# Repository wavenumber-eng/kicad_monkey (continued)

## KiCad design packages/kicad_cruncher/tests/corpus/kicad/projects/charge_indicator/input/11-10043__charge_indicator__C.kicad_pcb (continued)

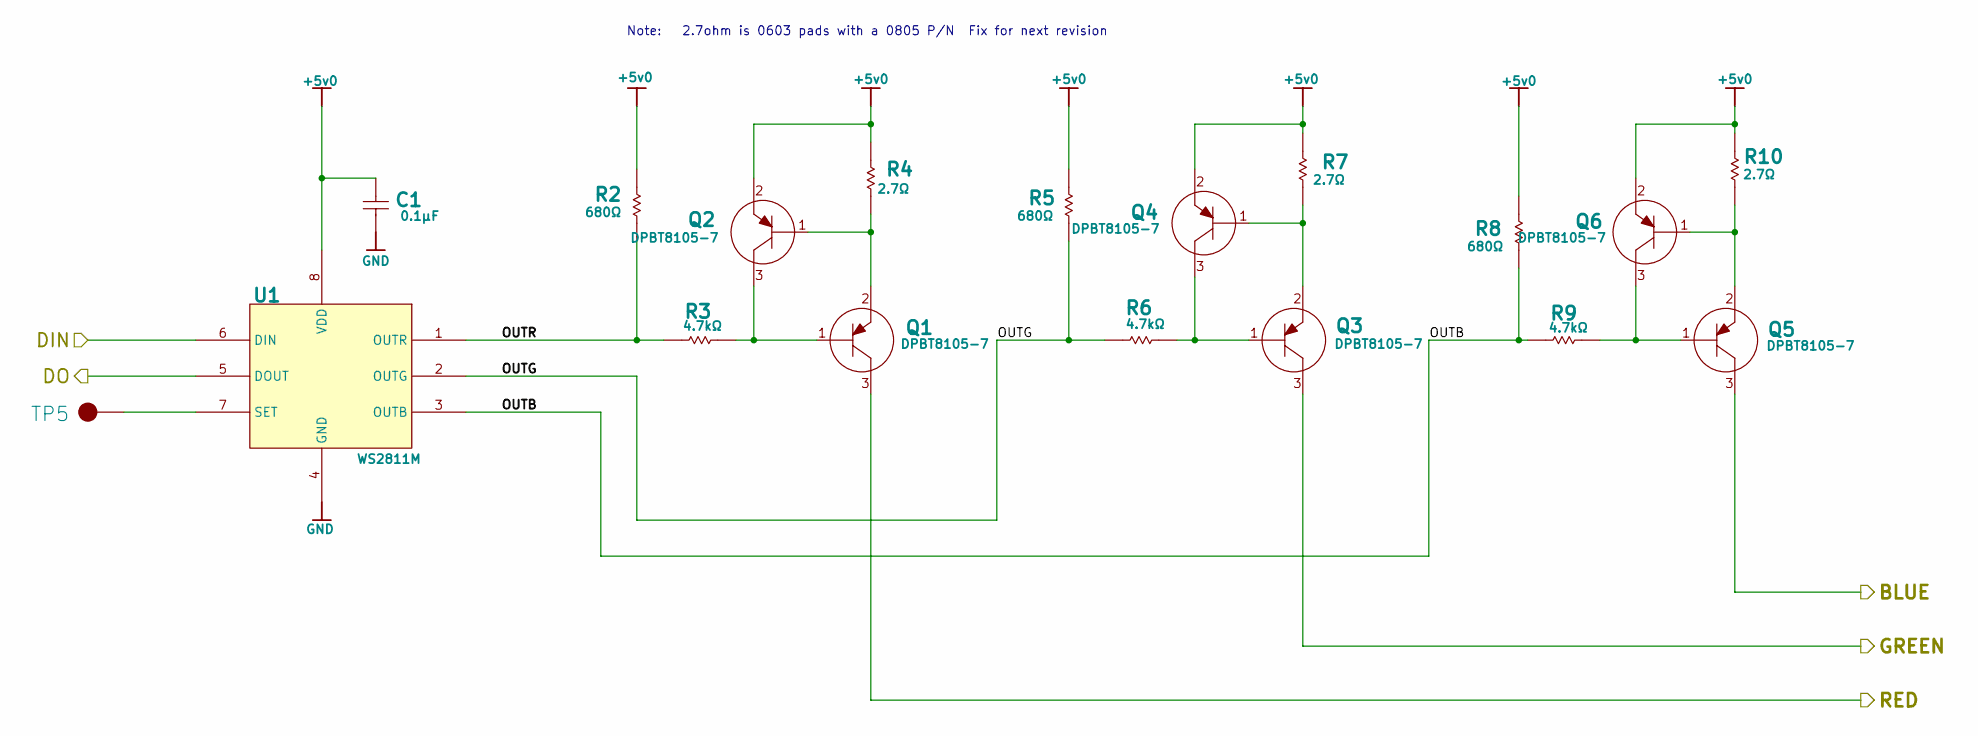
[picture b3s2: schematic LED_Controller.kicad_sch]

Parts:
1: Manufacturer Part Number Bugsly
C1: 0.1µF; C0603_0.90MM_MD; Manufacturer Part Number GCJ188R71C104KA01D
Q1, Q2, Q3, Q4, Q5, Q6: DPBT8105-7; SOT-23; Manufacturer Part Number DPBT8105-7
R2, R5, R8: 680Ω; R0603_0.55MM_MD; Manufacturer Part Number ERJ-3EKF6800V
R3, R6, R9: 4.7kΩ; R0603_0.55MM_MD; Manufacturer Part Number ERJ-3EKF4701V
R4, R7, R10: 2.7Ω; R0603_0.55MM_MD; Manufacturer Part Number ERJ-6RQF2R7V
TP5: SMT Testpoint 50mil; SMT_TP-50; Manufacturer Part Number SMT_TP-50
U1: WS2811M; MSOP8; Manufacturer Part Number WS2811M

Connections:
+5v0: C1.1, Q2.2 (E), Q4.2 (E), Q6.2 (E), R2.2, R4.2, R5.2, R7.2, R8.2, R10.2, U1.8 (VDD); also elsewhere on the board
/LED_Controller2/DO: U1.6 (DIN); also elsewhere on the board
/LED_Controller3/BLUE: Q5.3 (C); also elsewhere on the board
/LED_Controller3/DO: U1.5 (DOUT); also elsewhere on the board
/LED_Controller3/GREEN: Q3.3 (C); also elsewhere on the board
/LED_Controller3/OUTB: R8.1, R9.1, U1.3 (OUTB)
/LED_Controller3/OUTG: R5.1, R6.1, U1.2 (OUTG)
/LED_Controller3/OUTR: R2.1, R3.1, U1.1 (OUTR)
/LED_Controller3/RED: Q1.3 (C); also elsewhere on the board
GND: C1.2 (1), U1.4 (GND); also elsewhere on the board
unnamed: Q1.1 (B), Q2.3 (C), R3.2
unnamed: Q1.2 (E), Q2.1 (B), R4.1
unnamed: Q3.1 (B), Q4.3 (C), R6.2
unnamed: Q3.2 (E), Q4.1 (B), R7.1
unnamed: Q5.1 (B), Q6.3 (C), R9.2
unnamed: Q5.2 (E), Q6.1 (B), R10.1
unnamed: TP5.1, U1.7 (SET)

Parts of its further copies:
C2, C3, C4, C5: 0.1µF; C0603_0.90MM_MD; Manufacturer Part Number GCJ188R71C104KA01D
Q7, Q8, Q9, Q10, Q11, Q12, Q13, Q14, Q15, Q16, Q17, Q18, Q19, Q20, Q21, Q22, Q23, Q24, Q25, Q26, Q27, Q28, Q29, Q30: DPBT8105-7; SOT-23; Manufacturer Part Number DPBT8105-7
R12, R15, R18, R22, R25, R28, R32, R35, R38, R42, R45, R48: 680Ω; R0603_0.55MM_MD; Manufacturer Part Number ERJ-3EKF6800V
R13, R16, R19, R23, R26, R29, R33, R36, R39, R43, R46, R49: 4.7kΩ; R0603_0.55MM_MD; Manufacturer Part Number ERJ-3EKF4701V
R14, R17, R20, R24, R27, R30, R34, R37, R40, R44, R47, R50: 2.7Ω; R0603_0.55MM_MD; Manufacturer Part Number ERJ-6RQF2R7V
TP6, TP7, TP8, TP9: SMT Testpoint 50mil; SMT_TP-50; Manufacturer Part Number SMT_TP-50
U2, U3, U4, U5: WS2811M; MSOP8; Manufacturer Part Number WS2811M

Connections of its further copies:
+5v0: C2.1, C3.1, C4.1, C5.1, Q8.2 (E), Q10.2 (E), Q12.2 (E), Q14.2 (E), Q16.2 (E), Q18.2 (E), Q20.2 (E), Q22.2 (E), Q24.2 (E), Q26.2 (E), Q28.2 (E), Q30.2 (E), R12.2, R14.2, R15.2, R17.2, R18.2, R20.2, R22.2, R24.2, R25.2, R27.2, R28.2, R30.2, R32.2, R34.2, R35.2, R37.2, R38.2, R40.2, R42.2, R44.2, R45.2, R47.2, R48.2, R50.2, U2.8 (VDD), U3.8 (VDD), U4.8 (VDD), U5.8 (VDD); also elsewhere on the board
/DATA-IN: U3.6 (DIN); also elsewhere on the board
/DATA-OUT: U2.5 (DOUT); also elsewhere on the board
/LED_Controller2/BLUE: Q17.3 (C); also elsewhere on the board
/LED_Controller2/DO: U3.5 (DOUT); also elsewhere on the board
/LED_Controller2/GREEN: Q15.3 (C); also elsewhere on the board
/LED_Controller2/OUTB: R28.1, R29.1, U3.3 (OUTB)
/LED_Controller2/OUTG: R25.1, R26.1, U3.2 (OUTG)
/LED_Controller2/OUTR: R22.1, R23.1, U3.1 (OUTR)
/LED_Controller2/RED: Q13.3 (C); also elsewhere on the board
/LED_Controller3/DO: U4.6 (DIN); also elsewhere on the board
/LED_Controller4/BLUE: Q23.3 (C); also elsewhere on the board
/LED_Controller4/DO: U4.5 (DOUT), U5.6 (DIN)
/LED_Controller4/GREEN: Q21.3 (C); also elsewhere on the board
/LED_Controller4/OUTB: R38.1, R39.1, U4.3 (OUTB)
/LED_Controller4/OUTG: R35.1, R36.1, U4.2 (OUTG)
/LED_Controller4/OUTR: R32.1, R33.1, U4.1 (OUTR)
/LED_Controller4/RED: Q19.3 (C); also elsewhere on the board
/LED_Controller5/BLUE: Q29.3 (C); also elsewhere on the board
/LED_Controller5/DO: U2.6 (DIN), U5.5 (DOUT)
/LED_Controller5/GREEN: Q27.3 (C); also elsewhere on the board
/LED_Controller5/OUTB: R48.1, R49.1, U5.3 (OUTB)
/LED_Controller5/OUTG: R45.1, R46.1, U5.2 (OUTG)
/LED_Controller5/OUTR: R42.1, R43.1, U5.1 (OUTR)
/LED_Controller5/RED: Q25.3 (C); also elsewhere on the board
/LED_Controller6/BLUE: Q11.3 (C); also elsewhere on the board
/LED_Controller6/GREEN: Q9.3 (C); also elsewhere on the board
/LED_Controller6/OUTB: R18.1, R19.1, U2.3 (OUTB)
/LED_Controller6/OUTG: R15.1, R16.1, U2.2 (OUTG)
/LED_Controller6/OUTR: R12.1, R13.1, U2.1 (OUTR)
/LED_Controller6/RED: Q7.3 (C); also elsewhere on the board
GND: C2.2 (1), C3.2 (1), C4.2 (1), C5.2 (1), U2.4 (GND), U3.4 (GND), U4.4 (GND), U5.4 (GND); also elsewhere on the board
unnamed: Q7.1 (B), Q8.3 (C), R13.2
unnamed: Q7.2 (E), Q8.1 (B), R14.1
unnamed: Q9.2 (E), Q10.1 (B), R17.1
unnamed: Q9.1 (B), Q10.3 (C), R16.2
unnamed: Q11.1 (B), Q12.3 (C), R19.2
unnamed: Q11.2 (E), Q12.1 (B), R20.1
unnamed: Q13.1 (B), Q14.3 (C), R23.2
unnamed: Q13.2 (E), Q14.1 (B), R24.1
unnamed: Q15.1 (B), Q16.3 (C), R26.2
unnamed: Q15.2 (E), Q16.1 (B), R27.1
unnamed: Q17.1 (B), Q18.3 (C), R29.2
unnamed: Q17.2 (E), Q18.1 (B), R30.1
unnamed: Q19.1 (B), Q20.3 (C), R33.2
unnamed: Q19.2 (E), Q20.1 (B), R34.1
unnamed: Q21.1 (B), Q22.3 (C), R36.2
unnamed: Q21.2 (E), Q22.1 (B), R37.1
unnamed: Q23.1 (B), Q24.3 (C), R39.2
unnamed: Q23.2 (E), Q24.1 (B), R40.1
unnamed: Q25.1 (B), Q26.3 (C), R43.2
unnamed: Q25.2 (E), Q26.1 (B), R44.1
unnamed: Q27.1 (B), Q28.3 (C), R46.2
unnamed: Q27.2 (E), Q28.1 (B), R47.1
unnamed: Q29.1 (B), Q30.3 (C), R49.2
unnamed: Q29.2 (E), Q30.1 (B), R50.1
unnamed: TP6.1, U2.7 (SET)
unnamed: TP7.1, U3.7 (SET)
unnamed: TP8.1, U4.7 (SET)
unnamed: TP9.1, U5.7 (SET)

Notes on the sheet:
Note: 2.7ohm is 0603 pads with a 0805 P/N Fix for next revision

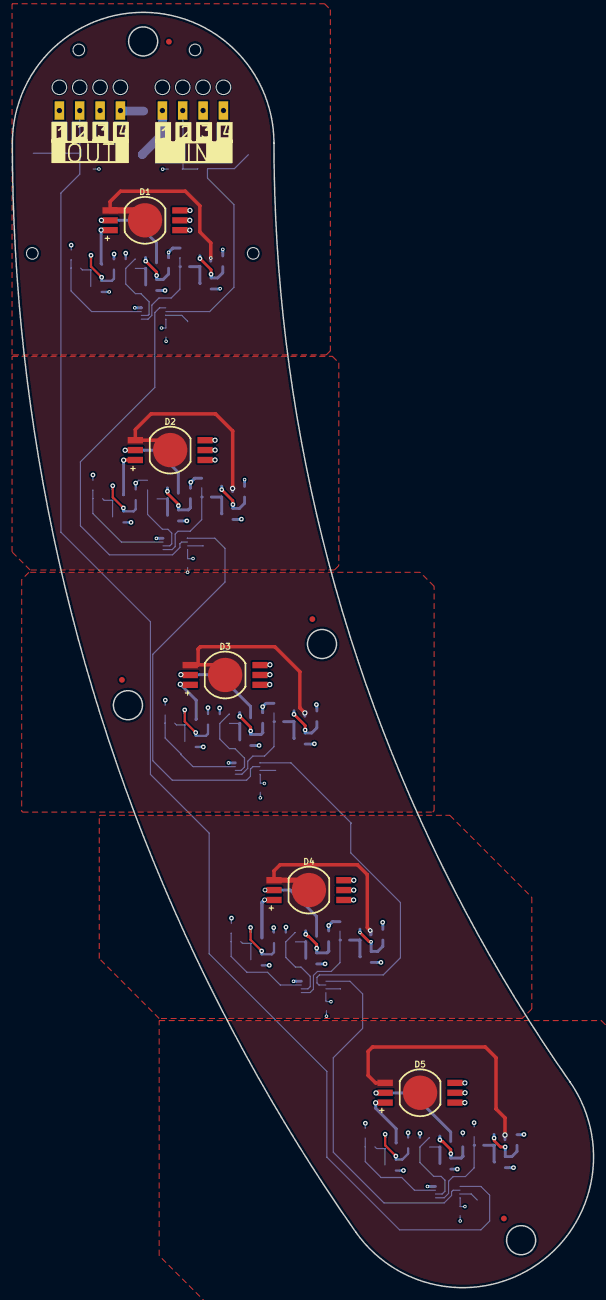
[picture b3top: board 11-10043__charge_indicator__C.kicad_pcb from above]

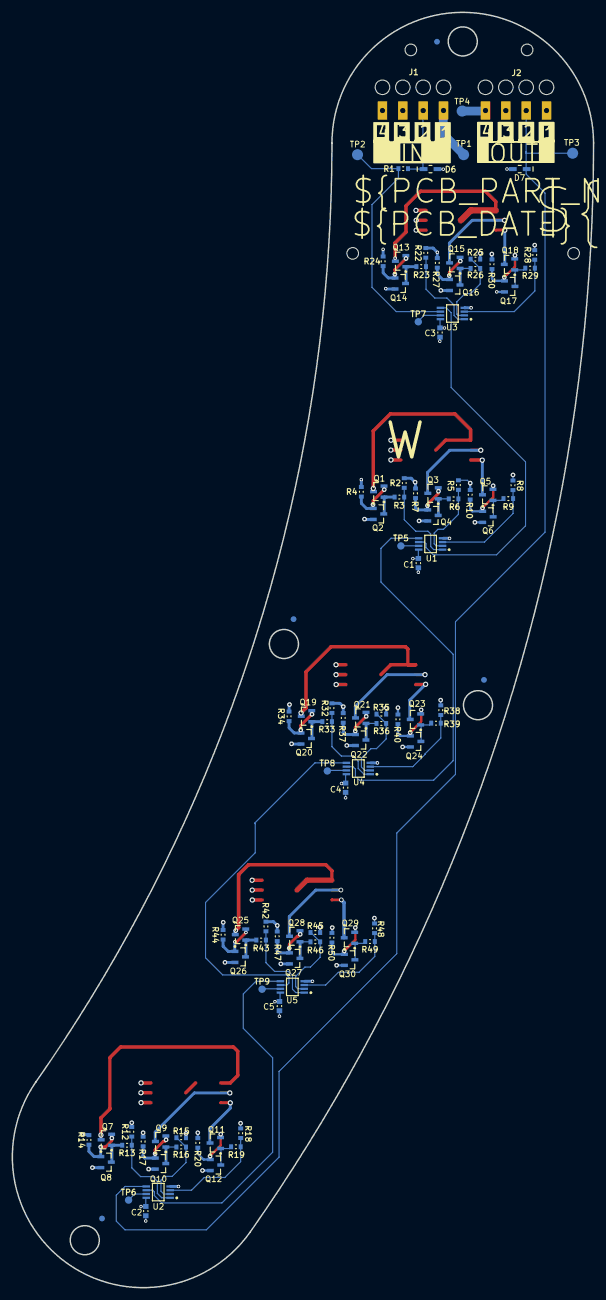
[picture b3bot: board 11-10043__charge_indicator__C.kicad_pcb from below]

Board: 4 copper layers, 100.0 x 219.4 mm, 112 parts (103 on the bottom side), 74 nets.
